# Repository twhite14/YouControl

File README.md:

# YouControl
An open source game controller for PC

##Requirements:
Arduino 1.8.1
Teensyduino 1.35
Teensy LC Microcontroller

##Getting started:
Install the Arduino IDE, then navigate to its path (either where you extracted it or C:\Program Files (x86)\Arduino\)
Navigate to hardware\teensy\avr\ and replace the boards.txt with the one in this repo's avr directory.
Navigate to hardware\teensy\avr\cores\teensy3\ and replace the files in that directory with those in this repo's teensy3 directory.
Test that the Buttons Arduino project compiles properly using both the standard Keyboard + Mouse + Joystick option and the YouControl copy.

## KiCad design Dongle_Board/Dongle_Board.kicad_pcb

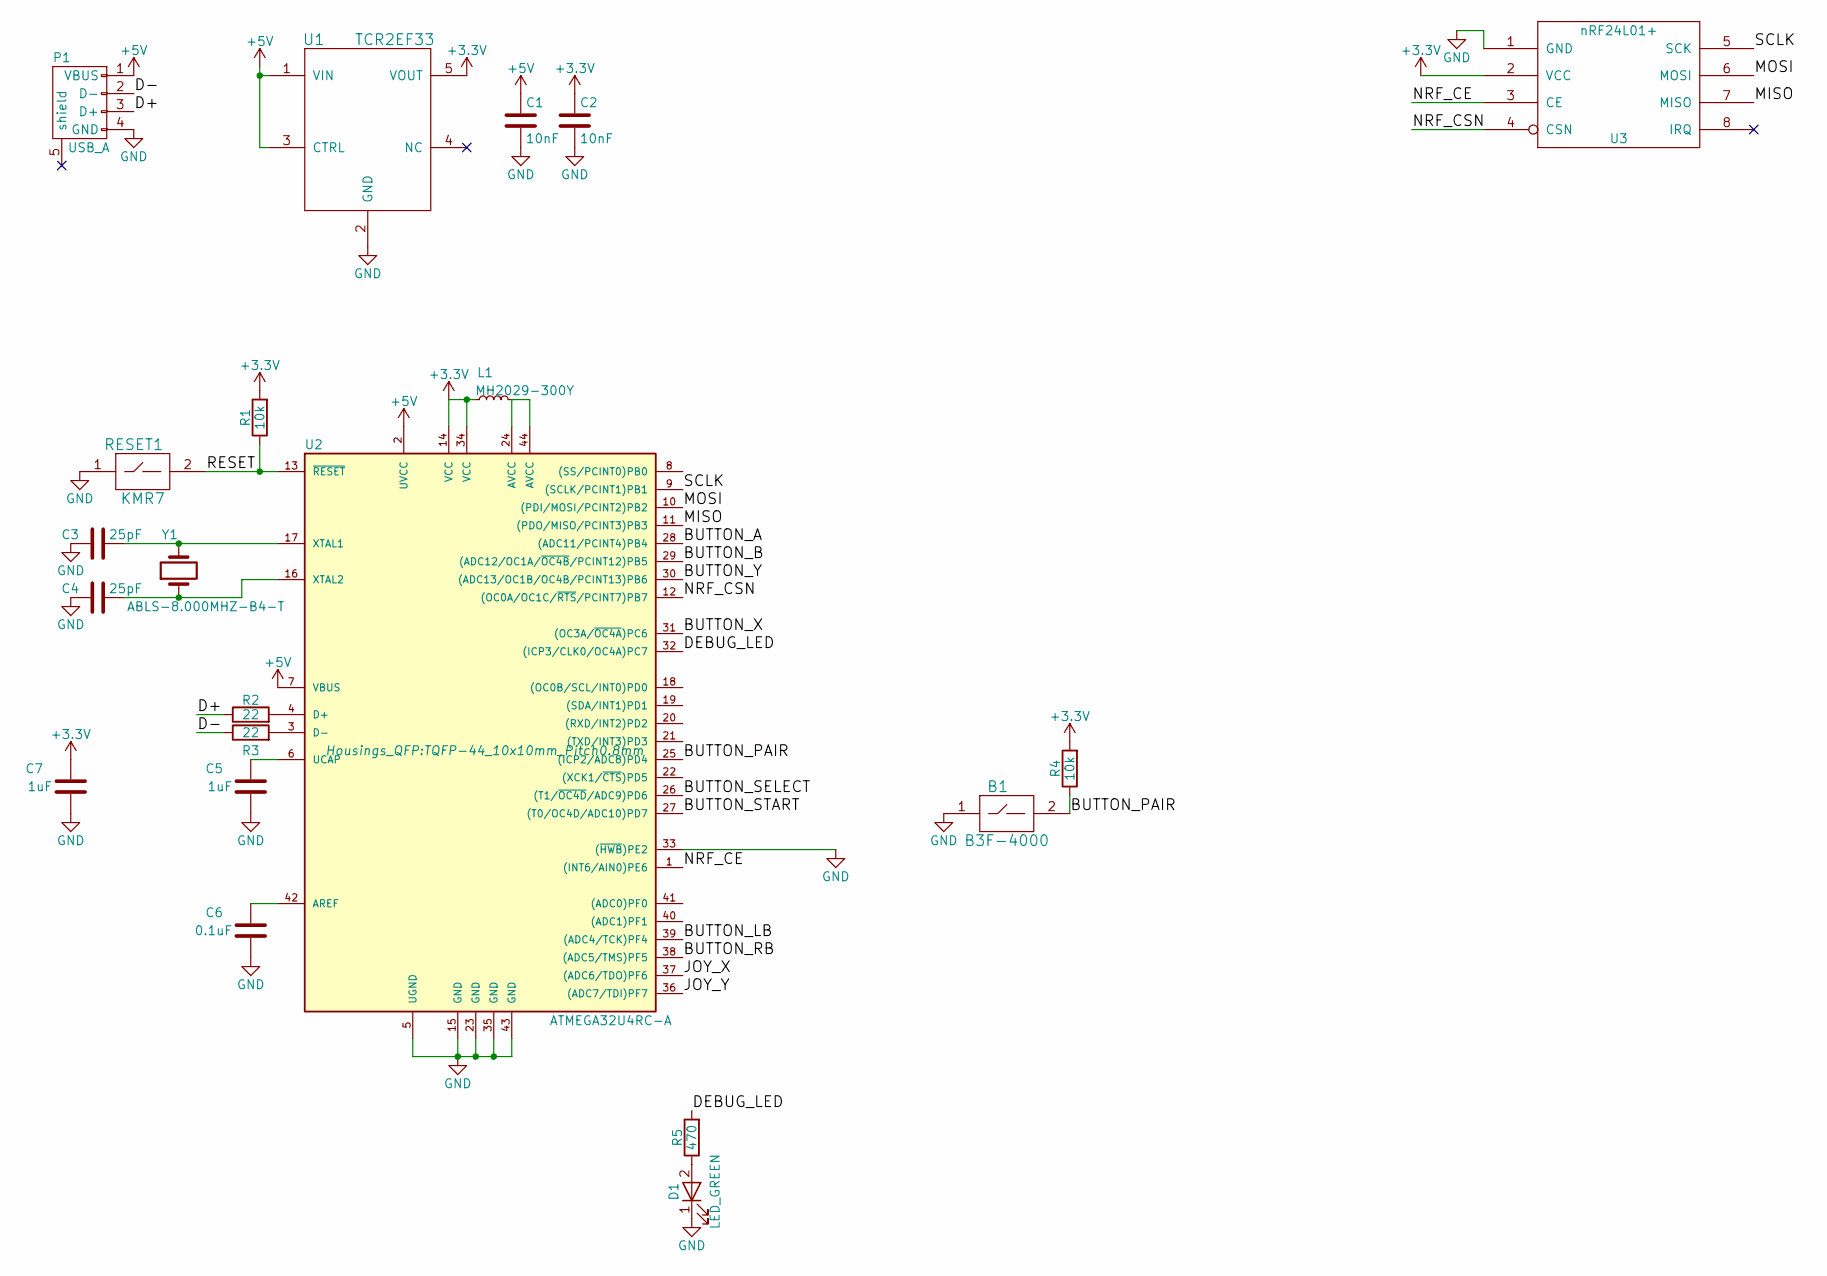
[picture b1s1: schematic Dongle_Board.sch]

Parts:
B1: B3F-4000; Button_Dual
C1, C2: 10nF; C_0603_HandSoldering
C3, C4: 25pF; C_0603_HandSoldering
C5, C7: 1uF; C_0603_HandSoldering
C6: 0.1uF; C_0603_HandSoldering
D1: LED_GREEN; D_0603
L1: MH2029-300Y; R_0805_HandSoldering
P1: USB_A; USB_A_No_Border
R1, R4: 10k; R_0603_HandSoldering
R2, R3: 22; R_0603_HandSoldering
R5: 470; R_0603_HandSoldering
RESET1: KMR7; SW_SPST_KMR2
U1: TCR2EF33; TSOT-23-5_HandSoldering
U2: ATMEGA32U4RC-A; TQFP-44_10x10mm_Pitch0.8mm
U3: nRF24L01+; nRF24L01_Breakout
Y1: ABLS-8.000MHZ-B4-T; Crystal_SMD_HC49-SD

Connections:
+3V3: C2.1, C7.2, L1.1, R1.2, R4.2, U1.5 (VOUT), U2.14 (VCC), U2.34 (VCC), U3.2 (VCC)
+5V: C1.1, P1.1 (VBUS), U1.1 (VIN), U1.3 (CTRL), U2.2 (UVCC), U2.7 (VBUS)
/BUTTON_A: U2.28 ((ADC11/PCINT4)PB4)
/BUTTON_B: U2.29 ((ADC12/OC1A/~OC4B~/PCINT12)PB5)
/BUTTON_LB: U2.39 ((ADC4/TCK)PF4)
/BUTTON_PAIR: B1.2, R4.1, U2.25 ((ICP2/ADC8)PD4)
/BUTTON_RB: U2.38 ((ADC5/TMS)PF5)
/BUTTON_SELECT: U2.26 ((T1/~OC4D~/ADC9)PD6)
/BUTTON_START: U2.27 ((T0/OC4D/ADC10)PD7)
/BUTTON_X: U2.31 ((OC3A/~OC4A~)PC6)
/BUTTON_Y: U2.30 ((ADC13/OC1B/OC4B/PCINT13)PB6)
/D+: P1.3 (D+), R2.1
/D-: P1.2 (D-), R3.1
/DEBUG_LED: R5.2, U2.32 ((ICP3/CLK0/OC4A)PC7)
/JOY_X: U2.37 ((ADC6/TDO)PF6)
/JOY_Y: U2.36 ((ADC7/TDI)PF7)
/MISO: U2.11 ((PDO/MISO/PCINT3)PB3), U3.7 (MISO)
/MOSI: U2.10 ((PDI/MOSI/PCINT2)PB2), U3.6 (MOSI)
/NRF_CE: U2.1 ((INT6/AIN0)PE6), U3.3 (CE)
/NRF_CSN: U2.12 ((OC0A/OC1C/~RTS~/PCINT7)PB7), U3.4 (CSN)
/RESET: R1.1, RESET1.2, U2.13 (~RESET~)
/SCLK: U2.9 ((SCLK/PCINT1)PB1), U3.5 (SCK)
GND: B1.1, C1.2, C2.2, C3.1, C4.1, C5.1, C6.1, C7.1, D1.1 (K), P1.4 (GND), RESET1.1, U1.2 (GND), U2.5 (UGND), U2.15 (GND), U2.23 (GND), U2.33 ((~HWB~)PE2), U2.35 (GND), U2.43 (GND), U3.1 (GND)
unnamed: C3.2, U2.17 (XTAL1), Y1.2
unnamed: C4.2, U2.16 (XTAL2), Y1.1
unnamed: C5.2, U2.6 (UCAP)
unnamed: C6.2, U2.42 (AREF)
unnamed: D1.2 (A), R5.1
unnamed: L1.2, U2.24 (AVCC), U2.44 (AVCC)
unnamed: R2.2, U2.4 (D+)
unnamed: R3.2, U2.3 (D-)

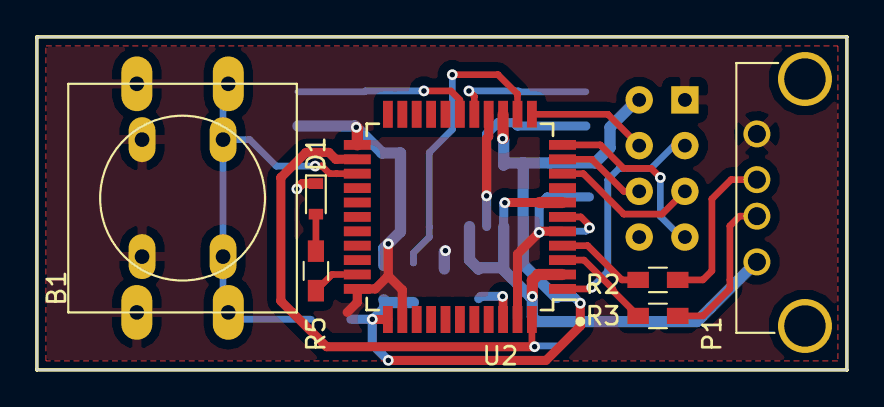
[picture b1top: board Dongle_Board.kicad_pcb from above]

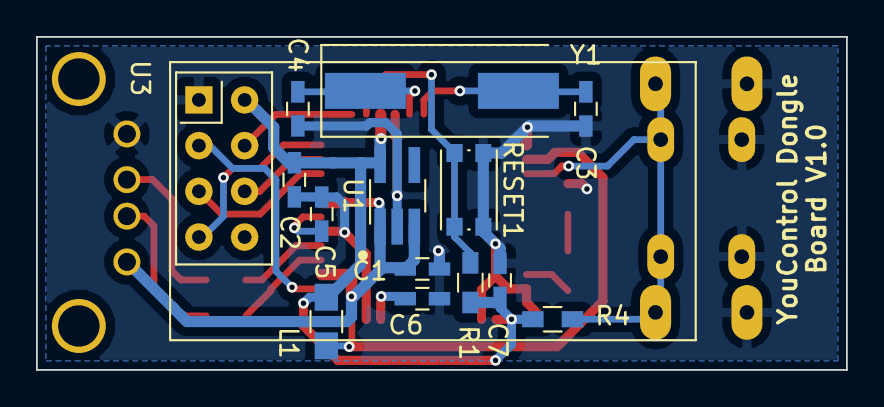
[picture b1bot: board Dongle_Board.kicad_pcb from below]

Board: 2 copper layers, 45.0 x 18.5 mm, 21 parts (14 on the bottom side), 21 nets.

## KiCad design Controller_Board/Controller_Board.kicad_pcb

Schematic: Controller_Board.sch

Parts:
B1, B2, B3, B4, B5, B6: B3F-4000; Button_Dual
B7, B8: B3F-4000; Button_Right_Angle
BATT1: S2B-PH-K-S; JST_PH_S2B-PH-K_02x2.00mm_Angled
C1, C2: 10nF; C_0603_HandSoldering
C3, C4: 25pF; C_0603_HandSoldering
C5, C7: 1uF; C_0603_HandSoldering
C6: 0.1uF; C_0603_HandSoldering
D1: LED_RED; D_0603
D2, D3: LED_GREEN; D_0603
ICSP1: ICSP; Socket_Strip_Straight_2x03_Pitch2.54mm
JS1: JOYSTICK; Joystick_PlayStation
JS2: JOYSTICK_Adafruit; Joystick_Adafruit
L1: MH2029-300Y; R_0805_HandSoldering
P1: USB_MICRO; USB_Micro-B
R1: 2k; R_0603_HandSoldering
R2: 0.05; R_0603_HandSoldering
R3, R4, R18: 470; R_0603_HandSoldering
R5, R6, R9, R10, R11, R12, R13, R14, R15, R16, R17, R19, R20: 10k; R_0603_HandSoldering
R7, R8: 22; R_0603_HandSoldering
RESET1: KMR7; SW_SPST_KMR2
SW1: OS102011MA1QN1; MHSS1105
U1: MCP73831; SOT-23-5_HandSoldering
U2: LTC2941; MSOP-8_3x3mm_Pitch0.65mm
U3: TCR2EF33; TSOT-23-5_HandSoldering
U4: ATMEGA32U4RC-A; TQFP-44_10x10mm_Pitch0.8mm
U5: nRF24L01+; nRF24L01_Breakout
U6: I2C_DISPLAY; I2C_Screen
U7: NC7WZ07; SOT-363_SC-70-6
Y1: ABLS-8.000MHZ-B4-T; Crystal_SMD_HC49-SD

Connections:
+3V3: C2.1, C7.2, JS1.2 (VCC), JS2.3, JS2.4, L1.1, R6.2, R9.2, R10.2, R11.2, R12.2, R13.2, R14.2, R15.2, R16.2, R17.2, R19.2, R20.2, U3.5 (VOUT), U4.14 (VCC), U4.34 (VCC), U5.2 (VCC), U6.1 (VCC), U7.5 (VCC)
+5V: C1.1, D1.2 (A), ICSP1.2 (VCC), P1.1 (VBUS), U1.4 (VDD), U4.2 (UVCC), U4.7 (VBUS)
+BATT: R2.1, SW1.2, U1.3 (VBAT), U2.1 (SENSE+)
/BUTTON_A: B1.2, R9.1, U4.28 ((ADC11/PCINT4)PB4)
/BUTTON_B: B2.2, R10.1, U4.29 ((ADC12/OC1A/~OC4B~/PCINT12)PB5)
/BUTTON_LB: B8.2, R20.1, U4.39 ((ADC4/TCK)PF4)
/BUTTON_RB: B7.2, R19.1, U4.38 ((ADC5/TMS)PF5)
/BUTTON_SELECT: B6.2, R14.1, U4.26 ((T1/~OC4D~/ADC9)PD6)
/BUTTON_START: B5.2, R13.1, U4.27 ((T0/OC4D/ADC10)PD7)
/BUTTON_X: B3.2, R11.1, U4.31 ((OC3A/~OC4A~)PC6)
/BUTTON_Y: B4.2, R12.1, U4.30 ((ADC13/OC1B/OC4B/PCINT13)PB6)
/D+: P1.3 (D+), R7.1
/D-: P1.2 (D-), R8.1
/DEBUG_LED: D3.2 (A), U4.32 ((ICP3/CLK0/OC4A)PC7)
/JOY_BUTTON: JS1.5 (SW), R15.1, U4.25 ((ICP2/ADC8)PD4)
/JOY_X: JS1.3 (VRX), JS2.5, U4.37 ((ADC6/TDO)PF6)
/JOY_Y: JS1.4 (VRY), JS2.2, U4.36 ((ADC7/TDI)PF7)
/MISO: ICSP1.1 (MISO), U4.11 ((PDO/MISO/PCINT3)PB3), U5.7 (MISO)
/MOSI: U4.10 ((PDI/MOSI/PCINT2)PB2), U5.6 (MOSI), U7.4 (Y2)
/MOSI_H: ICSP1.4 (MOSI), U7.3 (A2)
/NRF_CE: U4.1 ((INT6/AIN0)PE6), U5.3 (CE)
/NRF_CSN: U4.12 ((OC0A/OC1C/~RTS~/PCINT7)PB7), U5.4 (CSN)
/RESET: ICSP1.5 (RESET), R6.1, RESET1.2, U4.13 (~RESET~)
/SCK_H: ICSP1.3 (SCK), U7.1 (A1)
/SCL: R16.1, U2.3 (SCL), U4.18 ((OC0B/SCL/INT0)PD0), U6.3 (SCL)
/SCLK: U4.9 ((SCLK/PCINT1)PB1), U5.5 (SCK), U7.6 (Y1)
/SDA: R17.1, U2.6 (SDA), U4.19 ((SDA/INT1)PD1), U6.4 (SDA)
GND: B1.1, B2.1, B3.1, B4.1, B5.1, B6.1, B7.1, B8.1, BATT1.2 (-), C1.2, C2.2, C3.1, C4.1, C5.1, C6.1, C7.1, D2.1 (K), ICSP1.6 (GND), JS1.1 (GND), JS2.1, JS2.6, P1.5 (GND), R1.2, R18.1, RESET1.1, U1.2 (VSS), U2.2 (GND), U3.2 (GND), U4.5 (UGND), U4.15 (GND), U4.23 (GND), U4.33 ((~HWB~)PE2), U4.35 (GND), U4.43 (GND), U5.1 (GND), U6.2 (GND), U7.2 (GND)
unnamed: BATT1.1 (+), R2.2, U2.8 (SENSE-)
unnamed: C3.2, U4.17 (XTAL1), Y1.2
unnamed: C4.2, U4.16 (XTAL2), Y1.1
unnamed: C5.2, U4.6 (UCAP)
unnamed: C6.2, U4.42 (AREF)
unnamed: D1.1 (K), R3.2
unnamed: D2.2 (A), R4.1
unnamed: D3.1 (K), R18.2
unnamed: L1.2, U4.24 (AVCC), U4.44 (AVCC)
unnamed: R1.1, U1.5 (PROG)
unnamed: R3.1, R4.2, U1.1 (STAT)
unnamed: R5.1, SW1.1, U3.1 (VIN)
unnamed: R5.2, U2.7 (!AL/CC), U3.3 (CTRL)
unnamed: R7.2, U4.4 (D+)
unnamed: R8.2, U4.3 (D-)

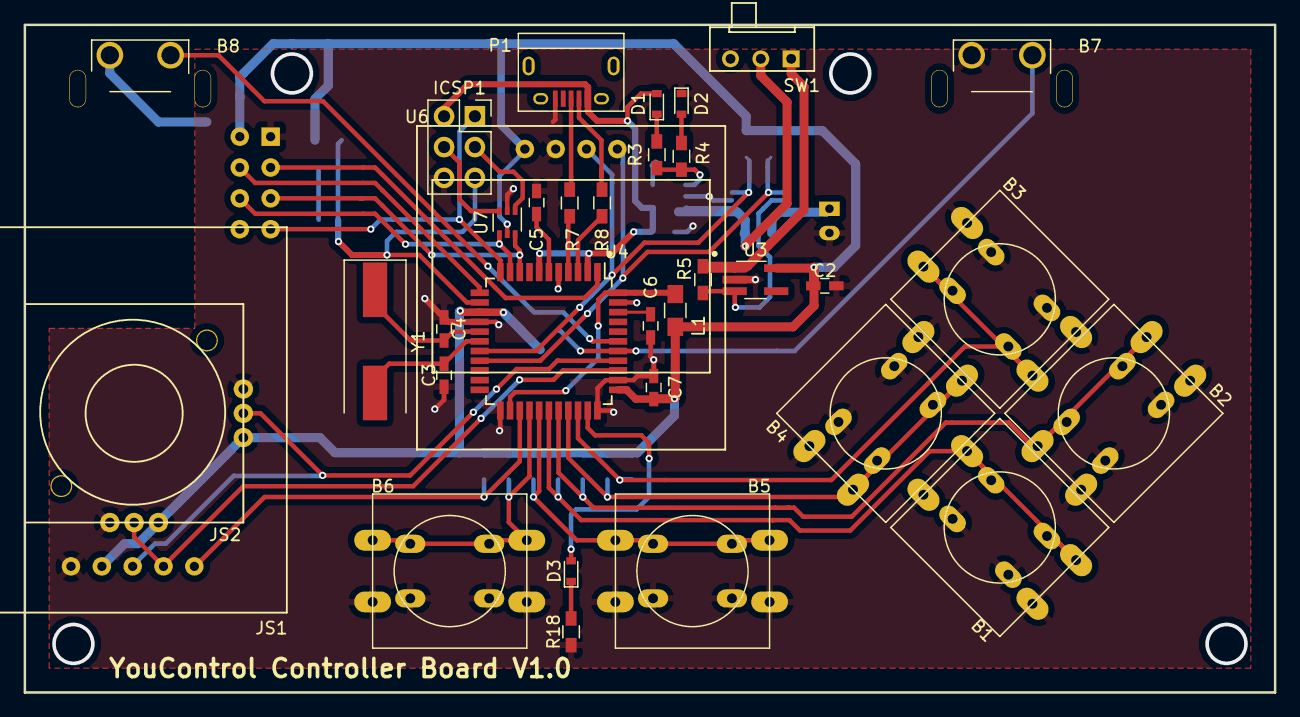
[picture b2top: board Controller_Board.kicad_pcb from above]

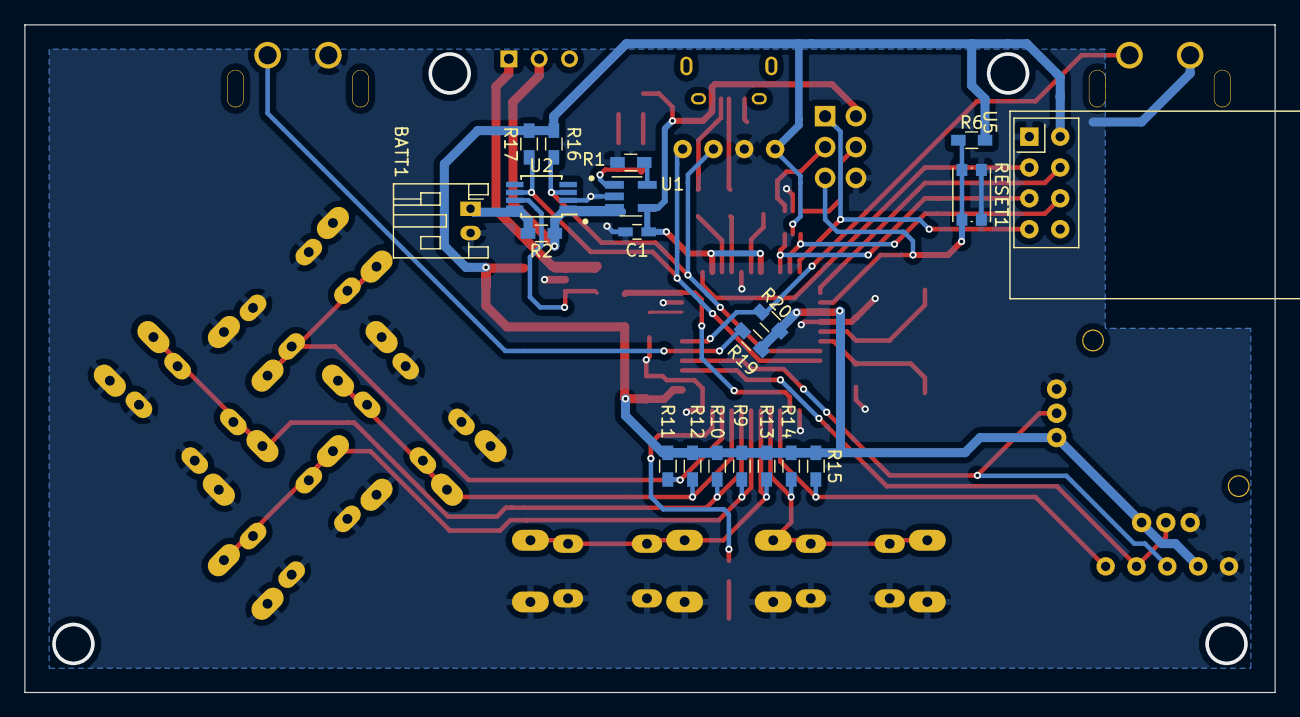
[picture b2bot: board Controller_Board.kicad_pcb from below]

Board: 2 copper layers, 103.0 x 55.0 mm, 54 parts (20 on the bottom side), 43 nets.

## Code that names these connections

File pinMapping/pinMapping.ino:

#include "Joystick.h"

//Controller pin mapping definitions
#define BUTTON_A      8
#define BUTTON_B      9
#define BUTTON_X      5
#define BUTTON_Y      10
#define BUTTON_RB     A2
#define BUTTON_LB     A3
#define BUTTON_JOY    4
#define BUTTON_START  6
#define BUTTON_SELECT 12
#define NRF_CE        7
#define NRF_CSN       11
#define DEBUG_LED     13
#define JOY_X         A1
#define JOY_Y         A0

#define NUM_BUTTONS   9

//Dongle joystick config definitions
#define JOY0_ID         3
#define JOY1_ID         4
#define JOY2_ID         5
#define JOY3_ID         6
#define JOY_TYPE        JOYSTICK_TYPE_GAMEPAD
#define HAT_SWITCHES    0
#define HAS_X_AXIS      true
#define HAS_Y_AXIS      true
#define HAS_Z_AXIS      false
#define HAS_RX_AXIS     false
#define HAS_RY_AXIS     false
#define HAS_RZ_AXIS     false
#define HAS_RUDDER      false
#define HAS_THROTTLE    false
#define HAS_ACCELERATOR false
#define HAS_BRAKE       false
#define HAS_STEERING    false

#define NUM_JOYSTICKS   4

//Joystick objects
Joystick_ Joystick[] = {
  Joystick_(JOY0_ID, JOY_TYPE, NUM_BUTTONS, HAT_SWITCHES, HAS_X_AXIS, HAS_Y_AXIS, HAS_Z_AXIS, HAS_RX_AXIS, HAS_RY_AXIS, HAS_RZ_AXIS, HAS_RUDDER, HAS_THROTTLE, HAS_ACCELERATOR, HAS_BRAKE, HAS_STEERING),
  Joystick_(JOY1_ID, JOY_TYPE, NUM_BUTTONS, HAT_SWITCHES, HAS_X_AXIS, HAS_Y_AXIS, HAS_Z_AXIS, HAS_RX_AXIS, HAS_RY_AXIS, HAS_RZ_AXIS, HAS_RUDDER, HAS_THROTTLE, HAS_ACCELERATOR, HAS_BRAKE, HAS_STEERING),
  Joystick_(JOY2_ID, JOY_TYPE, NUM_BUTTONS, HAT_SWITCHES, HAS_X_AXIS, HAS_Y_AXIS, HAS_Z_AXIS, HAS_RX_AXIS, HAS_RY_AXIS, HAS_RZ_AXIS, HAS_RUDDER, HAS_THROTTLE, HAS_ACCELERATOR, HAS_BRAKE, HAS_STEERING),
  Joystick_(JOY3_ID, JOY_TYPE, NUM_BUTTONS, HAT_SWITCHES, HAS_X_AXIS, HAS_Y_AXIS, HAS_Z_AXIS, HAS_RX_AXIS, HAS_RY_AXIS, HAS_RZ_AXIS, HAS_RUDDER, HAS_THROTTLE, HAS_ACCELERATOR, HAS_BRAKE, HAS_STEERING),
  };

//Button pins in order
int buttonPins[] = {BUTTON_A, BUTTON_B, BUTTON_X, BUTTON_Y, BUTTON_RB, BUTTON_LB, BUTTON_START, BUTTON_SELECT, BUTTON_JOY};

void setPinModes()
{
  for(int i = 0; i < NUM_BUTTONS; i++)
  {
    pinMode(buttonPins[i], INPUT);
  }
  pinMode(DEBUG_LED, OUTPUT);
  return;
}

//1 indicates Not Pressed, 0 indicates Pressed
uint16_t readButtons()
{
  uint16_t states;
  for(int i = 0; i < NUM_BUTTONS; i++)
  {
    states |= (digitalRead(buttonPins[i]) << i);
  }
  return states;
}

void writeButtons(uint8_t controller, uint16_t states)
{
  for(int i = 0; i < NUM_BUTTONS; i++)
  {
    if((states & (1<<i)) == 0)
    {
      Joystick[controller].pressButton(i+1);
    }
    else
    {
      Joystick[controller].releaseButton(i+1);
    }
  }
  return states;
}


void setup() {
  // put your setup code here, to run once:
  Serial.begin(9600);
}

void loop() {
  // put your main code here, to run repeatedly:

}

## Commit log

2017-02-10 Added joystick test program for Arduino Micro. Emulates 4 joysticks.
2017-02-11 Original Teensy files. Multijoystick functions to be added here
2017-02-11 Attempting to make a copy of keyboard/mouse/joystick interface
2017-02-11 Moved boards.txt to a more logical directory. Updated a few typos (previously overwrote other interface)
2017-02-11 Added Buttons test file to test my copy of keyboard/mouse/joystick. Works.
2017-02-11 Updated readme.
2017-02-14 Found a basic joystick tester compatible with Teensy
2017-02-14 Changed the dropdown menu name to indicate that it's a test (and no longer a keyboard/mouse)
2017-02-14 Modified copied HID descriptor to fit our profile. Will handle up to 4 controllers. Only supports one as of now
2017-02-14 Copied joystick descriptions and modified to match controller numbers. Adjusted USB descriptor sizes appropriately. Added new instances to USB configuration. Added new istances to Descriptor list.
2017-02-14 Finally created real instances of joysticks.
2017-02-14 Copied usb_joystick.c/h files to create joystick1.c/h. Added files (and placeholders for next) as #includes in WProgram.h.
2017-02-14 Updated joystick test programs for Micro and Teensy.
2017-02-14 Made copies of usb_joystick1.c/h and made them line up with joysticks 2-4.
2017-02-14 Uncommented lines now that necessary header files and definitions are available. Updated number of interfaces and endpoints in usb_desc.h
2017-02-16 Fixed a typo in array offsets
2017-03-05 Created controller board schematic in KiCad
2017-03-05 Placed almost all connections, power connections to follow
2017-03-27 Updated Controller Board with shoulder buttons, mounting holes, slightly altered pinout, second analog stick option, dual button footprints.... I really should have done this in stages...
2017-03-27 Created Dongle Board, a copy of the Controller Board minus the extra buttons and with a USB A connector instead of a micro USB. Also realize now that a controller could just as well act as a dongle i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
2017-03-30 Updated Dongle and Controller boards, ready for fab
2017-04-18 Added pinmapping file
2017-04-28 added final code used for demo
    initial_dongle_sketch is for the usb side
    initial_controller_sketch is for the controller with psp style joystick
    initial_controller_sketch_largejs is for the controller with 360-style joystick
2017-04-29 Removed references to Teensy
